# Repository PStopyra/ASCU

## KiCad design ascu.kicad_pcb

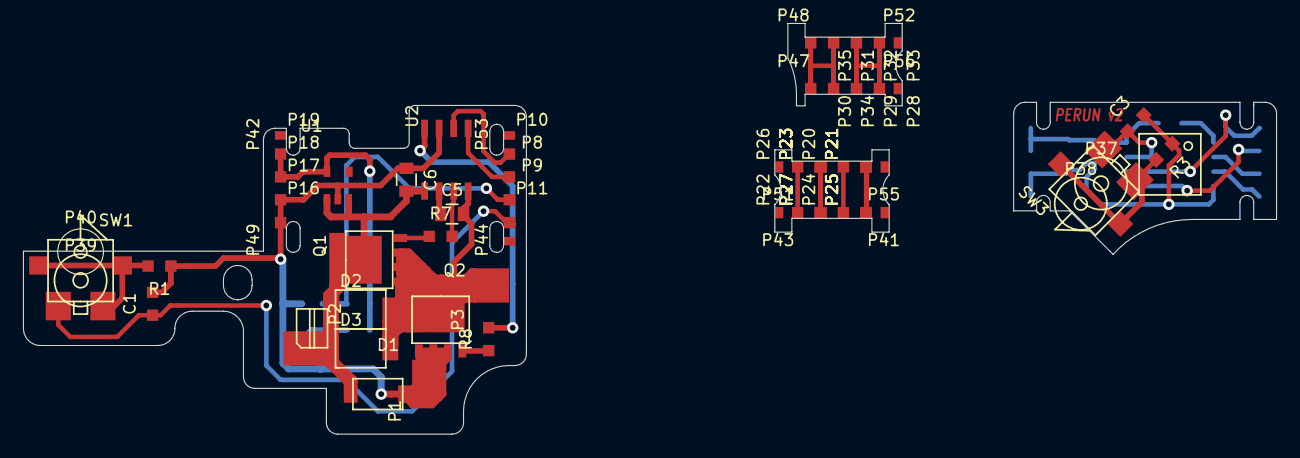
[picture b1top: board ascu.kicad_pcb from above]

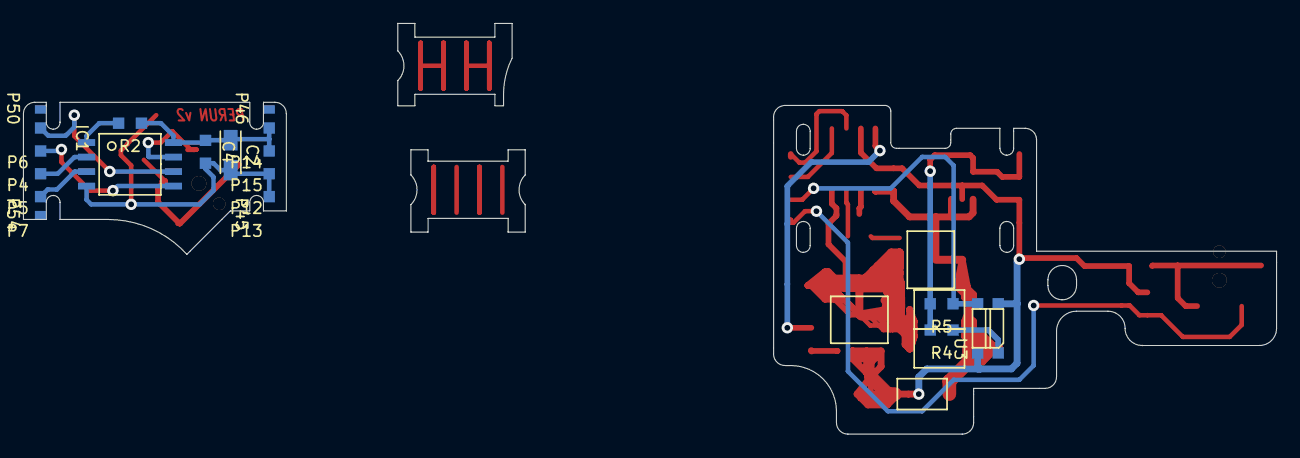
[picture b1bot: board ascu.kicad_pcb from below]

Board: 2 copper layers, 109.6 x 35.9 mm, 91 parts (19 on the bottom side), 30 nets.

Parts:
C1, C3, C4: 100n/10V; C_0805
C2: 10uF/10V; TantalC_SizeA_EIA-3216_Reflow
C5, C6: 10uF/25V; C_0805
D1: 15V/15A; DO-221AC
D2, D3: D; SOD-128
IC1: ATTINY25-SS; WSOIC8
P1: B-; 1_pin_smd_3x3
P2: B+S+; 1_pin_smd_3x3
P3: S-; 1_pin_smd_3x3
P4, P5, P6, P7, P8, P9, P10, P11, P12, P13, P14, P15, P16, P17, P18, P19, P20, P21, P21#2, P21#3, P21#4, P22, P23, P23#2, P23#3, P23#4, P24, P25, P25#2, P25#3, P25#4, P26, P27, P27#2, P27#3, P27#4, P28, P29, P30, P31, P32, P33, P34, P35: CONN_01X01; 1_pin_smd_1x1
P37, P38, P39, P40: Otwór; 1pin
P41, P42, P43, P44, P45, P46, P47, P48, P49, P50, P51, P52, P53, P54, P55, P56: Lut; Lut_1.5x0.75mm
Q1, Q2: PSMN1R2; SOT-669
R1, R3: 100; R_0805_HandSoldering
R2, R5: 10K; R_0805_HandSoldering
R4: 220R; R_0805_HandSoldering
R7, R8: 22R; R_0805_HandSoldering
SW1: DETECT; ESE-31R15T
SW3: TRIGGER; ESE-31L11T
U1: SPX3819; SOT-23-5_Przetwornica
U2: MIC4605; SO8
U3: TLP291; KTIR0711S

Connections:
5: C2.1, C4.1, IC1.8, P14.1, P15.1, R2.1
51: P30.1, P31.1, P34.1, P35.1
+5V: P18.1, P19.1, R4.2, R5.2, U1.5
DETECT: C1.1, P11.1, SW1.2
DETECT1: IC1.3, P7.1
DETECT11: P23.1, P23#2.1, P23#3.1, P23#4.1, P27.1, P27#2.1, P27#3.1, P27#4.1
G: C2.2, C3.2, C4.2, IC1.4, P12.1, P13.1, R3.1
G1: P28.1, P29.1, P32.1, P33.1
GND: C1.2, C6.1, D1.2, P1.1, P16.1, P17.1, Q2.3, R1.1, U1.2, U2.7, U3.2, U3.3
HIN: P8.1, U2.5
HIN1: IC1.5, P4.1
HIN11: P20.1, P24.1
HO: R7.2, U2.3
HS: C5.2, D2.2, D3.2, P3.1, Q1.3, Q2.2, U2.4
LIN: P10.1, U2.6
LIN1: IC1.6, P6.1
LIN11: P22.1, P26.1
LO: R8.2, U2.8
unnamed: C5.1, U2.2
unnamed: Q1.1, R7.1
unnamed: Q2.1, R8.1
unnamed: R1.2, SW1.1
unnamed: R3.2, SW3.1
unnamed: R4.1, U3.1
RESET: IC1.1, R2.2
SELECTOR: P9.1, R5.1, U3.4
SELECTOR1: IC1.2, P5.1
SELECTOR11: P21.1, P21#2.1, P21#3.1, P21#4.1, P25.1, P25#2.1, P25#3.1, P25#4.1
TRIGGER: C3.1, IC1.7, SW3.2
VCC: C6.2, D1.1, D2.1, D3.1, P2.1, Q1.2, U1.1, U1.3, U2.1

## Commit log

2016-09-22 :confetti_ball: Added .gitattributes & .gitignore files
2016-09-22 0805 Zamiast 0603
    Zmiana mniejszych obudów rezystorów na większe
2016-09-22 Dodanie szerokiej obudowy
2016-09-22 Test
    test
2016-09-22 Poprawki
2016-09-22 Revert "Poprawki"
    This reverts commit 9021c68e6a4ef5e3f9d6ce24ccd05bc863d9a415.
